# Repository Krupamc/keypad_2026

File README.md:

# My Linux-looking Macropad
The name is a work in progress I know haha. This is my macropad, a small custom shortcut pad with several layers of shortcuts that are changed through the rotary encoder. Different LEDs light up and the OLED with update with the current layer and appropriate image. I created this in order to increase my productivity and overall workflow of my desk.
---

## Features:
- 128x32 OLED Display for customized layer imagary
- EC11 Rotary encoder to switch between layers.
- 5 Layer LEDs to coordinate with the layers (will activate one by one and change colors; layer 0 has 1 navy blue LEDs, layer 1 has 2 dark blue LEDs).
  - (Colors are customizable) 
- 4 Keys
- 1 Status/Ambient LED
- Being a really cool thing to flex.
---
## PCB:
The PCB (Printed Circuit Board) was created using KiCad. Awesome open source software.
You can open the PCB here:

### Schematic: 

Here is the plan for the PCB laid out with my wiring.

### PCB:

Very cool looking PCB. I added as much silkscreen I could to really sell the terminal-inspired design.

## CAD:

I created a case in Fusion. Excuse how it is not very good/original as it is my first time doing CAD before. I have two parts: the bottom and top case. 
### Bottom Case:
The bottom case is a box with standoffs to hold (on the top-right, and bottom-left) the PCB. M3x16mm screws go through the screw holes on the bottom through the standoffs. The bottom case also has a single foot that has a 40° angle for one inch. (same as my current keyboard to be consistant) The foot has small circle indents for rubber feet in future or hot glue. There is also a USB-C cutout for the microcontroller 

### Top Case:  
This section has extrusions for heat inserts to go (for the screws mentioned before) as well as holes for the OLED, LEDs, keys, and the rotary encoder.

---

## Firmware Functions:
Coded in KMK (Micro-python based keyboard framework). On each layer, a configurable photo, text splash and color (for LEDs) is shown. The number of LEDs active is based on the layer number.

Right now the short cuts include:
- Copy, Paste, Undo, Redo
- CTRL + F, clipboard, File explorer, Screenshots
- Pause unpause, mute discord mic, defen discord, mute pc

Planned to add ones for games I play/other applications later.

---

## BOM:
- 1X Seeed XIAO RP2040
- 1x 0.91" 128x32 OLED Display
- 4x Cherry MX Switches
- 4x DSA Keycaps
- 1x EC11E Rotary encoders
- 6x SK6812 MINI-E LEDs
- 2x M3x16mm screws
- 2x M3x5mx4mm heatset inserts
- 3x Parts for 3D Case (Top, Bottom, and Knob).

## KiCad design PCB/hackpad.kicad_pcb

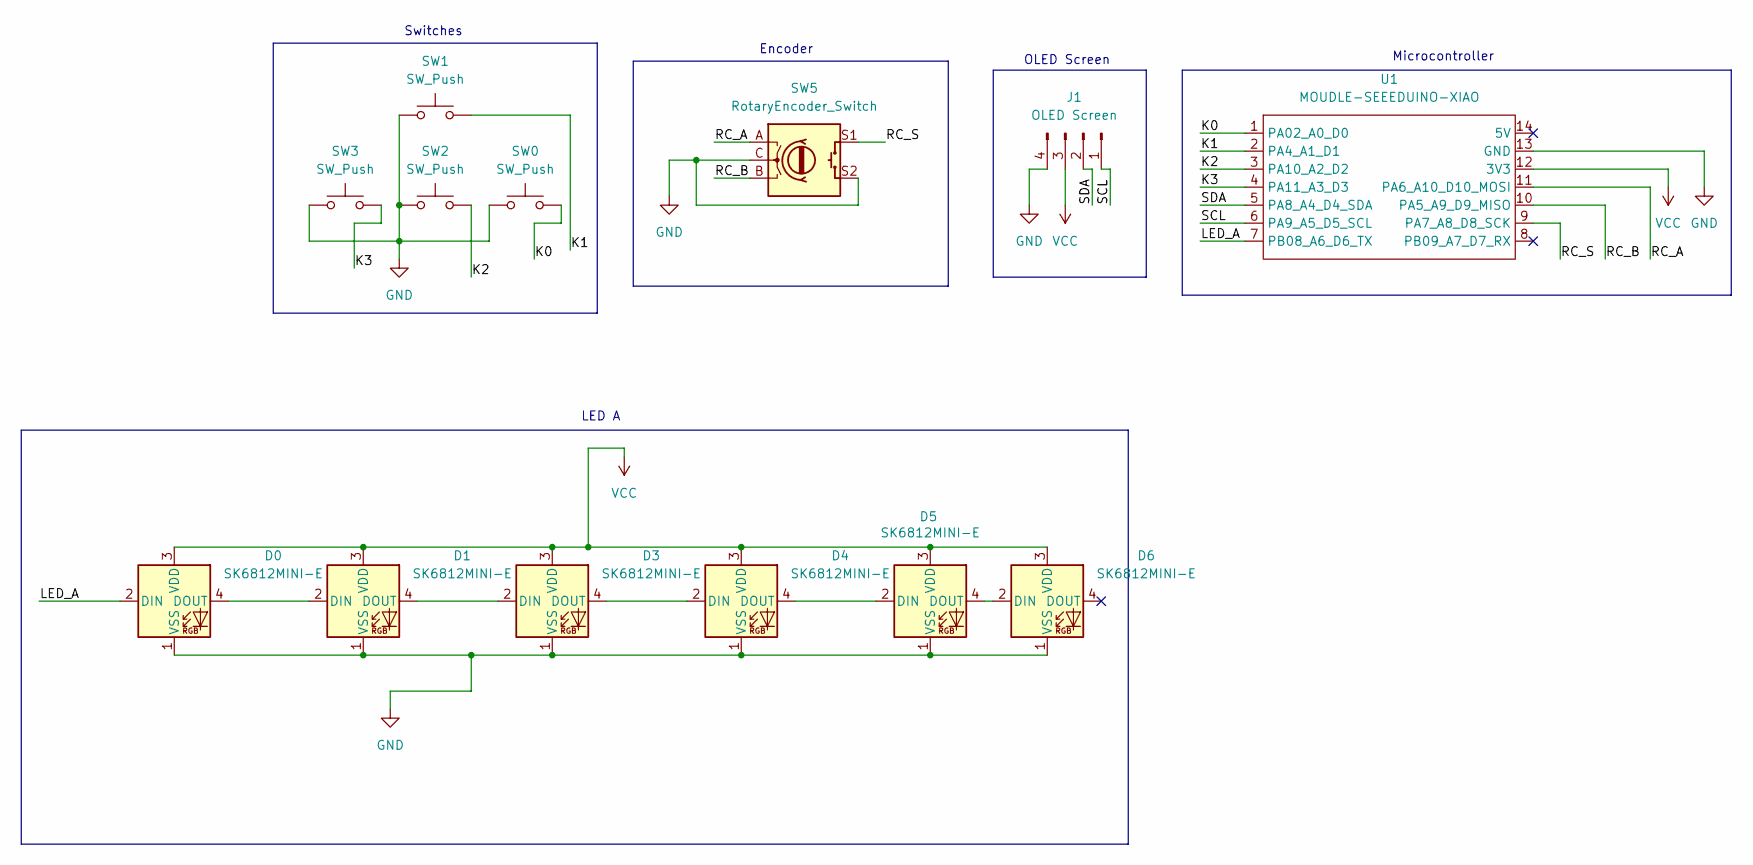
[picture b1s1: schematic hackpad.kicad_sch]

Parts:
D0, D1, D3, D4, D5, D6: SK6812MINI-E; LED_OPSCO_SK6812_PLCC4_5.0x5.0mm_P3.1mm
J1: OLED Screen; PinHeader_1x04_P2.54mm_Vertical
SW0, SW1, SW2, SW3: SW_Push; SW_Cherry_MX_1.00u_PCB
SW5: RotaryEncoder_Switch; RotaryEncoder_Alps_EC11E-Switch_Vertical_H20mm
U1: MOUDLE-SEEEDUINO-XIAO; XIAO-Generic-Hybrid-14P-2.54-21X17.8MM

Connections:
/K0: SW0.2, U1.1 (PA02_A0_D0)
/K1: SW1.2, U1.2 (PA4_A1_D1)
/K2: SW2.2, U1.3 (PA10_A2_D2)
/K3: SW3.2, U1.4 (PA11_A3_D3)
/LED_A: D0.2 (DIN), U1.7 (PB08_A6_D6_TX)
/RC_A: SW5.A, U1.11 (PA6_A10_D10_MOSI)
/RC_B: SW5.B, U1.10 (PA5_A9_D9_MISO)
/RC_S: SW5.S1, U1.9 (PA7_A8_D8_SCK)
/SCL: J1.1, U1.6 (PA9_A5_D5_SCL)
/SDA: J1.2, U1.5 (PA8_A4_D4_SDA)
GND: D0.1 (VSS), D1.1 (VSS), D3.1 (VSS), D4.1 (VSS), D5.1 (VSS), D6.1 (VSS), J1.4, SW0.1, SW1.1, SW2.1, SW3.1, SW5.C, SW5.S2, U1.13 (GND)
unnamed: D0.4 (DOUT), D1.2 (DIN)
unnamed: D1.4 (DOUT), D3.2 (DIN)
unnamed: D3.4 (DOUT), D4.2 (DIN)
unnamed: D4.4 (DOUT), D5.2 (DIN)
unnamed: D5.4 (DOUT), D6.2 (DIN)
VCC: D0.3 (VDD), D1.3 (VDD), D3.3 (VDD), D4.3 (VDD), D5.3 (VDD), D6.3 (VDD), J1.3, U1.12 (3V3)

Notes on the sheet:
Microcontroller
Switches
OLED Screen
Encoder
LED A

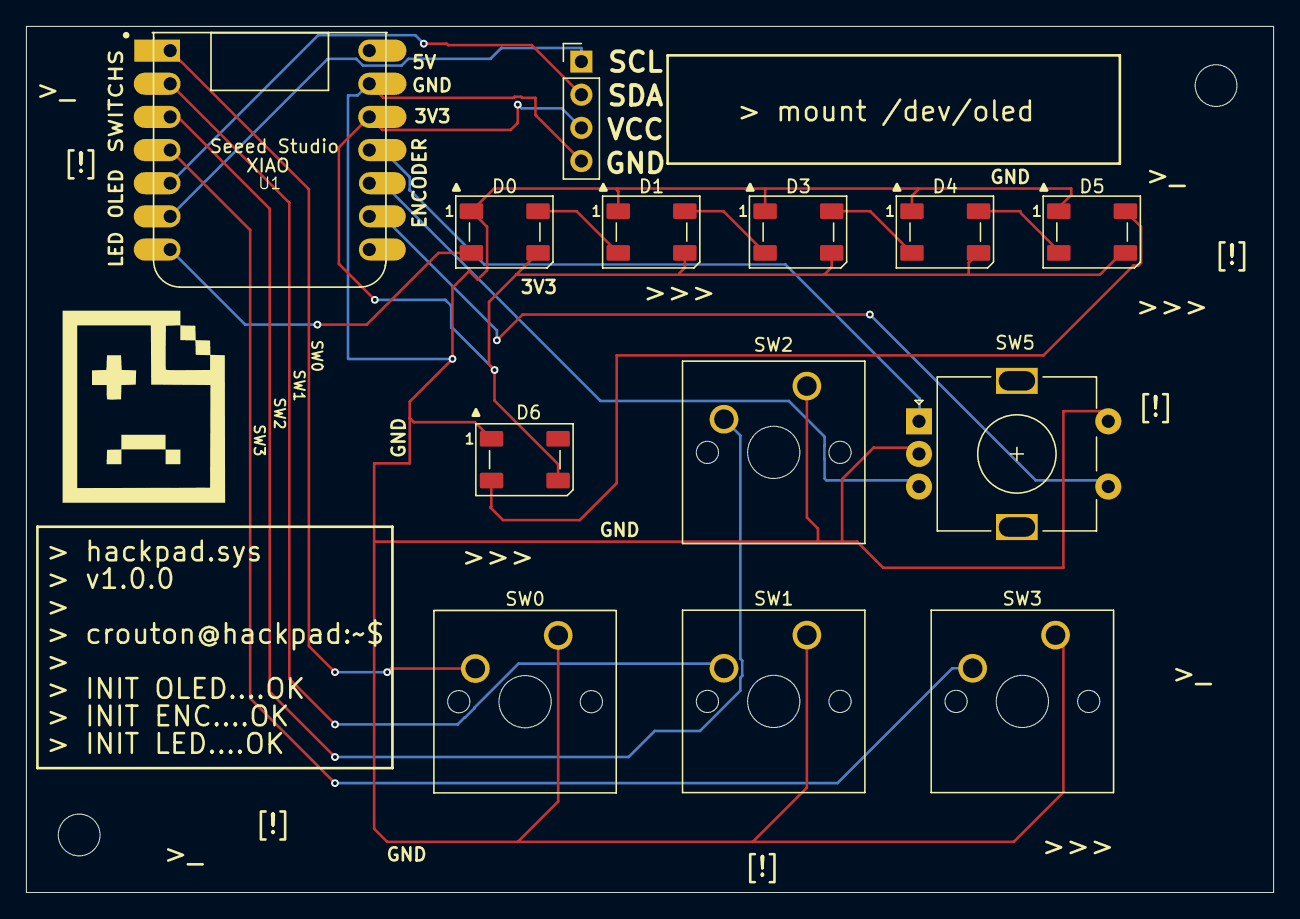
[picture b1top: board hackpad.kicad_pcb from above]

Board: 2 copper layers, 95.5 x 66.4 mm, 13 parts (0 on the bottom side), 17 nets.
